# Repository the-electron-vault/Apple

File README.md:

# Apple

## Overview
This repository contains resources relating to Apple products.

## Disclaimer
The information contained in this repository has been generated via reverse-engineering of publicly available material, and is provided without warranty or guarantee of accuracy. [The Electron Vault](https://www.theelectronvault.com/) is not responsible for any losses or damages caused to equipment as a consequence of the information contained in this repository or associated documents.

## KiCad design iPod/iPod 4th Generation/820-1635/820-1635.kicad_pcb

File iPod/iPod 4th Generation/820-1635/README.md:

# 820-1635 iPod 4th Generation (Monochrome) Headphone/Hold Switch Board

## Overview
This is an open-source, KiCad-based 820-1635 PCBA that has been reverse-engineered from a physical board. This is the Headphone Jack and Hold Switch board used in the 4th Generation Monochrome iPod.

## Disclaimer
The information contained in this repository has been generated via reverse-engineering of publicly available material, and is provided without warranty or guarantee of accuracy. [The Electron Vault](https://www.theelectronvault.com/) is not responsible for any losses or damages caused to equipment as a consequence of the information contained in this repository or associated documents.

## Setup
### Database Library
This project uses a local database library for all components. As the library is linked to the project through relative pathing, it should just work once the ODBC driver is installed.
1) Install an ODBC driver. I use this one http://www.ch-werner.de/sqliteodbc/
2) [Optional] Install an SQLite database editor. I use SQLiteStudio https://sqlitestudio.pl

### Theme
This KiCad project has a number of thematic customisations. These are however completely optional and everything *should* work fine with the default theme. If you however wish to install the theme, here is the procedure:
1) Install KiCad as normal.
2) Copy PREF/color/Black and White.json from the repo into the corresponding folder in your KiCad preferences.
3) Launch KiCad and open Preferences -> Colors.
4) The Black and White theme should now be available in Schematic Editor -> Colors and PCB Editor -> Colors.
5) Schematic font: Arial

## Known Limitations
As this is a reverse-engineered design, there are several limitations potentially affecting accuracy that must be acknowledged:
- **This board is not ready for production.** The intent was to make it visually accurate enough to assist with troubleshooting and repair. OpenBoardView (Landrex-BRD) compatible files (generated using [kicad-boardview](https://github.com/whitequark/kicad-boardview) exporter) are provided in the repo along with PDF schematics.
- Component placement is only photographically accurate - there may be mechanical interferences.
- Board outline is best-effort. Use at your own risk.
- Board stackup is best effort; likely 4-layer.
- All routing is best-effort **and incomplete**, primarily as a checklist aid/sanity check that nets have been assigned to the correct components. There are missing elements such as internal planes/poly-pours.
- Trace widths are purely photographically scaled.
- Passive component (resistors, capacitors) values were measured with an LCR meter and rounded to the nearest standard value. Accuracy is not guaranteed.
- Some effort was made to characterise ferrite beads. The VNA scans can be found in the DOC folder. The part numbers captured in the schematic are **equivalent substitutes based on these scans and provided without guarantee.**
- The original part numbers for the buzzer, spring contacts, and hold switch were not able to be identified and thus equivalent substitutes were used.

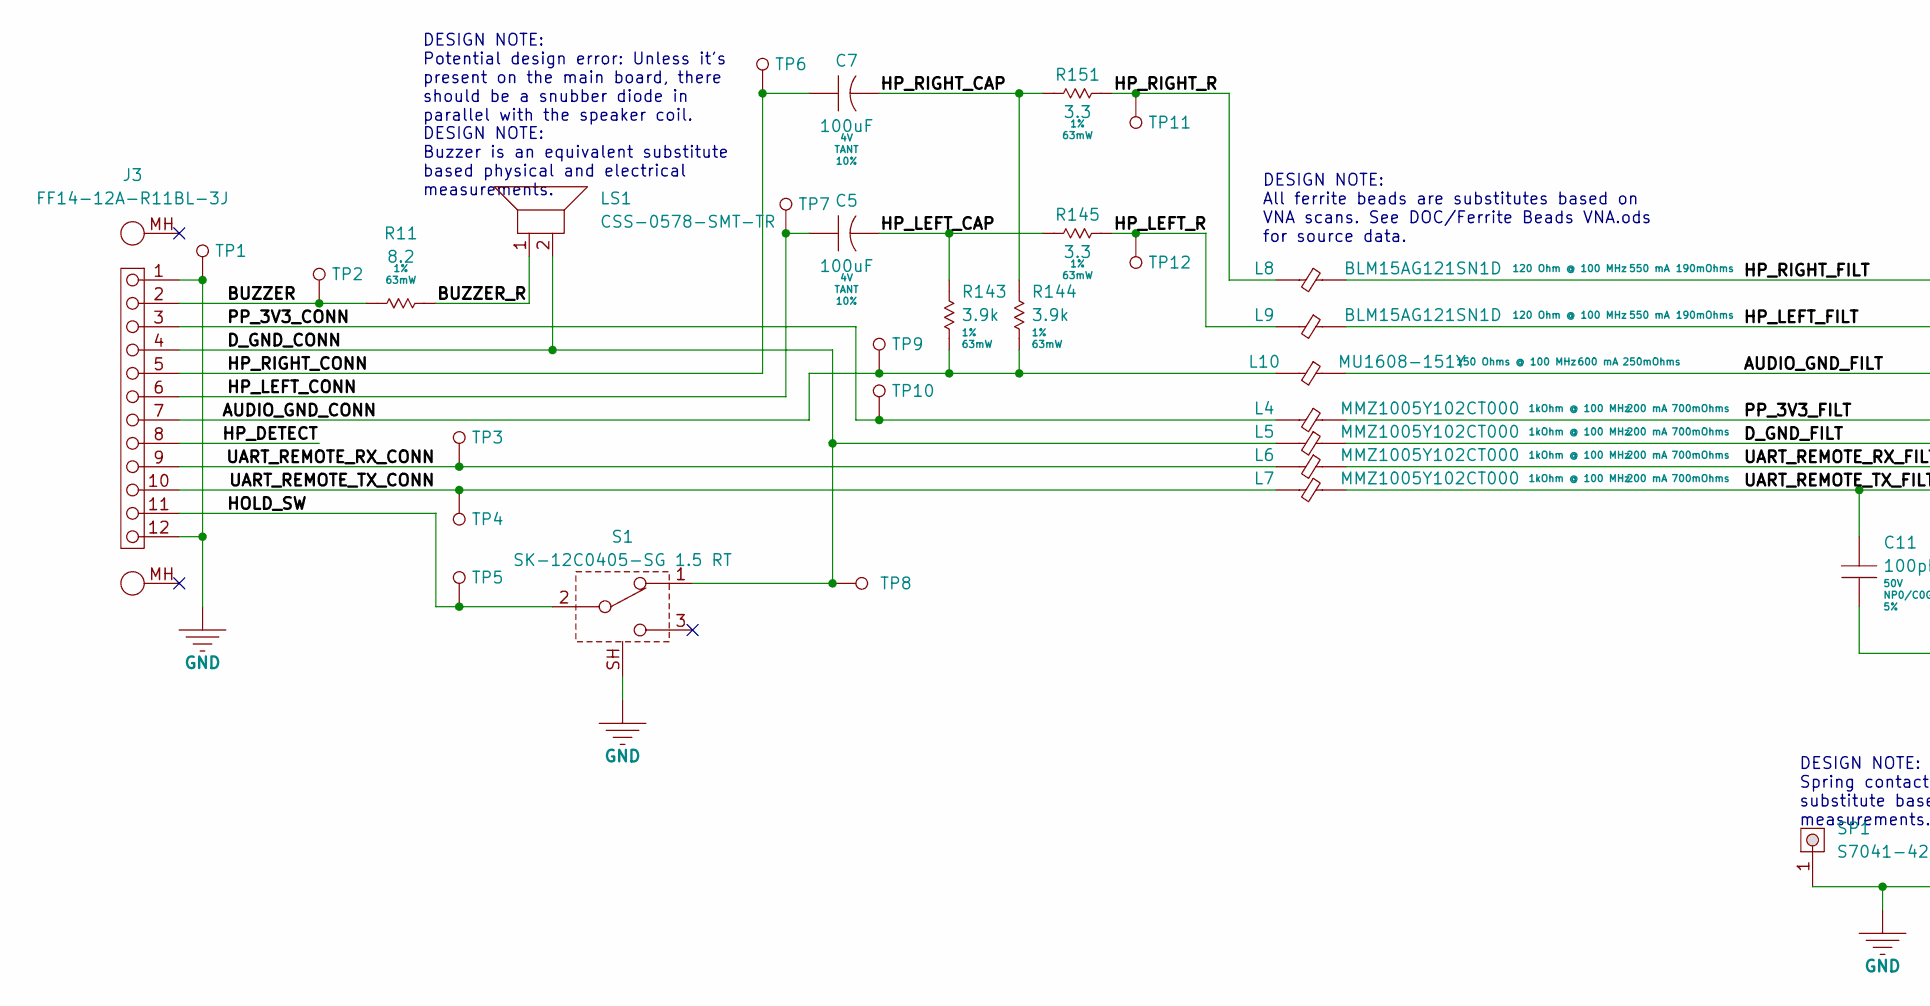
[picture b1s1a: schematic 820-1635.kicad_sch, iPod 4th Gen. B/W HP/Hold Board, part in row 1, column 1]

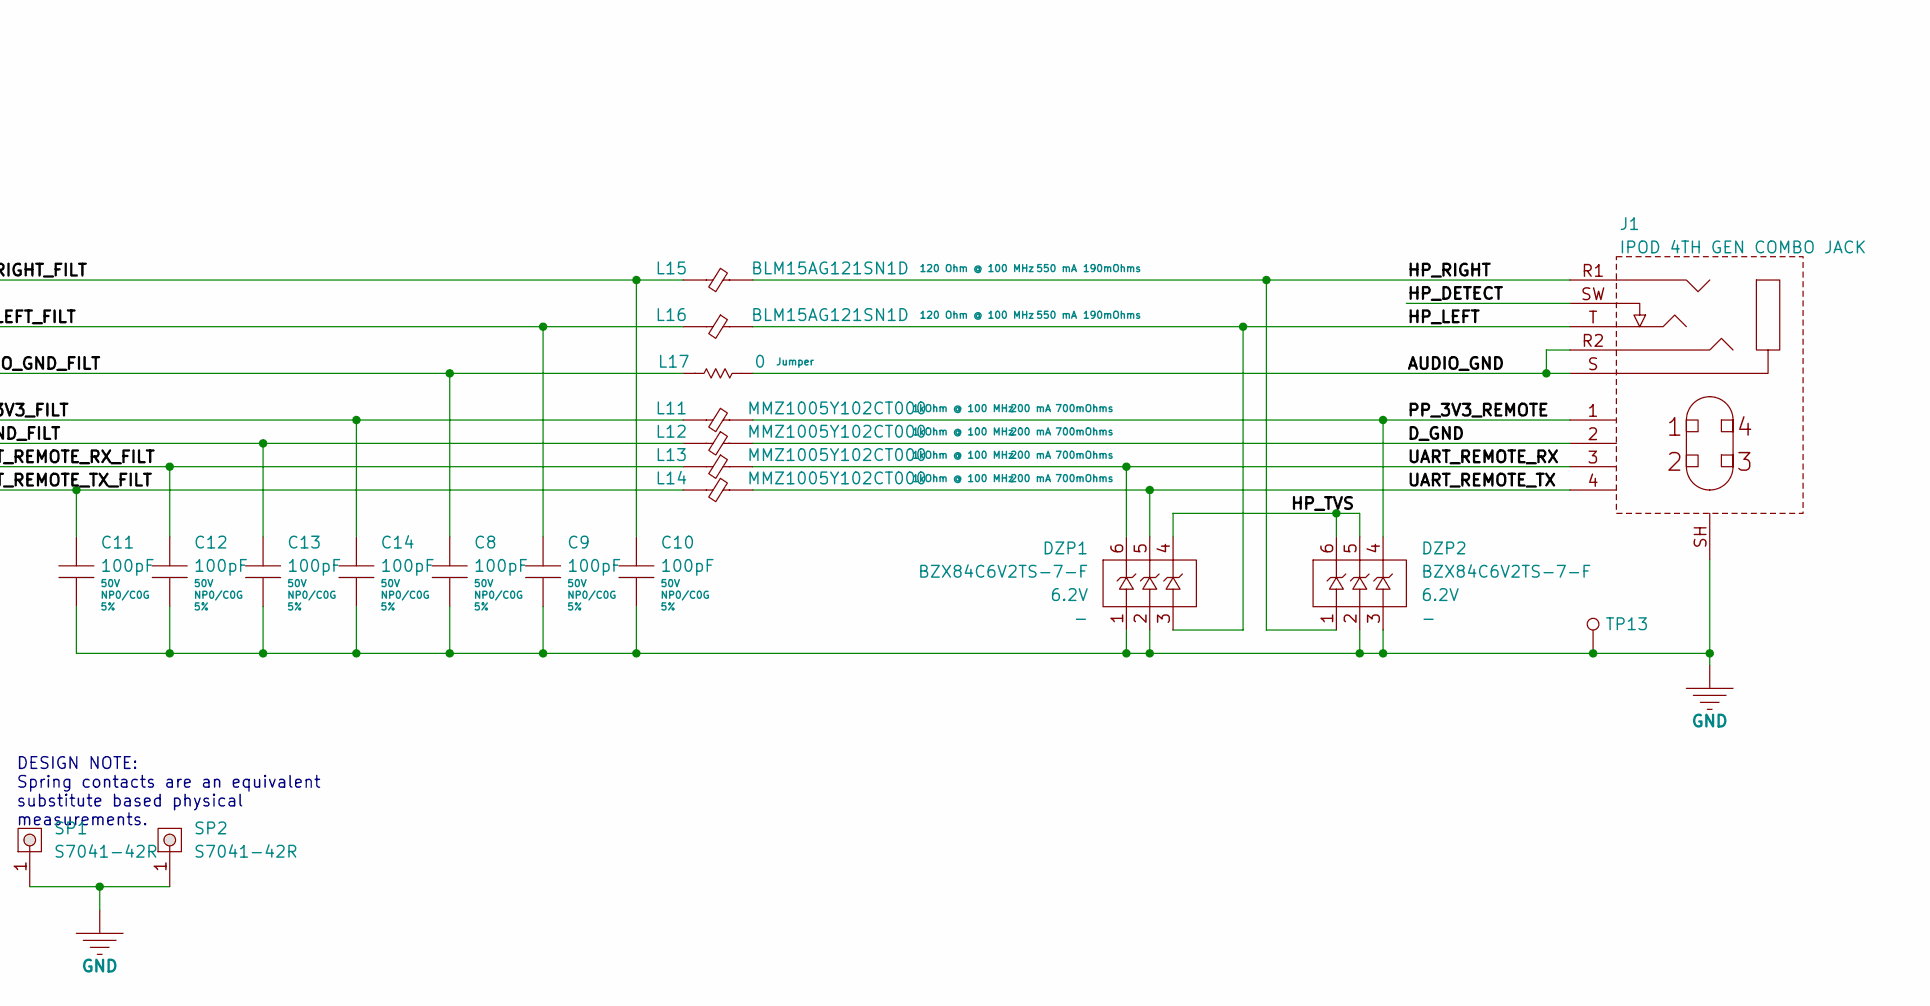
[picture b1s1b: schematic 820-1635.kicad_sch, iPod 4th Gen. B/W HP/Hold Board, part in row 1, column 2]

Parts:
C5, C7: 100uF; TPS-B; Voltage 4V; Tolerance 10%; Manufacturer Part Number TPSB107K004R0250
C8, C9, C10, C11, C12, C13, C14: 100pF; MLCC-0402; Voltage 50V; Tolerance 5%; Manufacturer Part Number CL05C101JB5NNNC
DZP1, DZP2: BZX84C6V2TS-7-F; SOT-363; Voltage 6.2V; Manufacturer Part Number BZX84C6V2TS-7-F
J1: IPOD 4TH GEN COMBO JACK; COMBO-JACK; Manufacturer Part Number IPOD 4TH GEN COMBO JACK
J3: FF14-12A-R11BL-3J; FF14-12A-R11B; Manufacturer Part Number FF14-12A-R11BL-3J
L4, L5, L6, L7, L11, L12, L13, L14: MMZ1005Y102CT000; FB-0402; Manufacturer Part Number MMZ1005Y102CT000
L8, L9, L15, L16: BLM15AG121SN1D; FB-0402; Manufacturer Part Number BLM15AG121SN1D
L10: MU1608-151Y; FB-0603; Manufacturer Part Number MU1608-151Y
L17: 0; RES-0603; Tolerance Jumper; Manufacturer Part Number CRCW06030000Z0EA
LS1: CSS-0578-SMT-TR; Manufacturer Part Number CSS-0578-SMT-TR
R11: 8.2; RES-0402; Tolerance 1%; Manufacturer Part Number CRCW04028R20FKEDC
R143, R144: 3.9k; RES-0402; Tolerance 1%; Manufacturer Part Number CRCW04023K90FKEDC
R145, R151: 3.3; RES-0402; Tolerance 1%; Manufacturer Part Number CRCW04023R30FKEDC
S1: SK-12C0405-SG 1.5 RT; Manufacturer Part Number SK-12C0405-SG 1.5 RT
SP1, SP2: S7041-42R; Manufacturer Part Number S7041-42R
TP1, TP2, TP3, TP4, TP5, TP6, TP7, TP8, TP9, TP10, TP11, TP12, TP13: TP; TP-SMT-0.6mm

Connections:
/AUDIO_GND: J1.R2 (RING2), J1.S (SLEEVE), L17.2
/AUDIO_GND_CONN: J3.7, L10.1, R143.2, R144.2, TP9.1
/AUDIO_GND_FILT: C8.1, L10.2, L17.1
/BUZZER: J3.2, R11.1, TP2.1
/BUZZER_R: LS1.1, R11.2
/D_GND: J1.2, L12.2
/D_GND_CONN: J3.4, L5.1, LS1.2, S1.1, TP8.1
/D_GND_FILT: C13.1, L5.2, L12.1
/HOLD_SW: J3.11, S1.2, TP5.1
/HP_DETECT: J1.SW (TIP_SWITCH), J3.8
/HP_LEFT: DZP1.3 (K2), J1.T (TIP), L16.2
/HP_LEFT_CAP: C5.2, R143.1, R145.1
/HP_LEFT_CONN: C5.1, J3.6, TP7.1
/HP_LEFT_FILT: C9.1, L9.2, L16.1
/HP_LEFT_R: L9.1, R145.2, TP12.1
/HP_RIGHT: DZP2.1 (A1), J1.R1 (RING1), L15.2
/HP_RIGHT_CAP: C7.2, R144.1, R151.1
/HP_RIGHT_CONN: C7.1, J3.5, TP6.1
/HP_RIGHT_FILT: C10.1, L8.2, L15.1
/HP_RIGHT_R: L8.1, R151.2, TP11.1
/HP_TVS: DZP1.4 (C3), DZP2.5 (C2), DZP2.6 (C1)
/PP_3V3_CONN: J3.3, L4.1, TP10.1
/PP_3V3_FILT: C14.1, L4.2, L11.1
/PP_3V3_REMOTE: DZP2.4 (C3), J1.1, L11.2
/UART_REMOTE_RX: DZP1.6 (C1), J1.3, L13.2
/UART_REMOTE_RX_CONN: J3.9, L6.1, TP3.1
/UART_REMOTE_RX_FILT: C12.1, L6.2, L13.1
/UART_REMOTE_TX: DZP1.5 (C2), J1.4, L14.2
/UART_REMOTE_TX_CONN: J3.10, L7.1, TP4.1
/UART_REMOTE_TX_FILT: C11.1, L7.2, L14.1
GND: C8.2, C9.2, C10.2, C11.2, C12.2, C13.2, C14.2, DZP1.1 (A1), DZP1.2 (S2), DZP2.2 (S2), DZP2.3 (K2), J1.SH, J3.1, J3.12, S1.SH, SP1.1, SP2.1, TP1.1, TP13.1

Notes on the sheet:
DESIGN NOTE: Potential design error: Unless it's present on the main board, there should be a snubber diode in parallel with the speaker coil.
DESIGN NOTE: Spring contacts are an equivalent substitute based physical measurements.
DESIGN NOTE: All ferrite beads are substitutes based on VNA scans. See DOC/Ferrite Beads VNA.ods for source data.
DESIGN NOTE: Buzzer is an equivalent substitute based physical and electrical measurements.

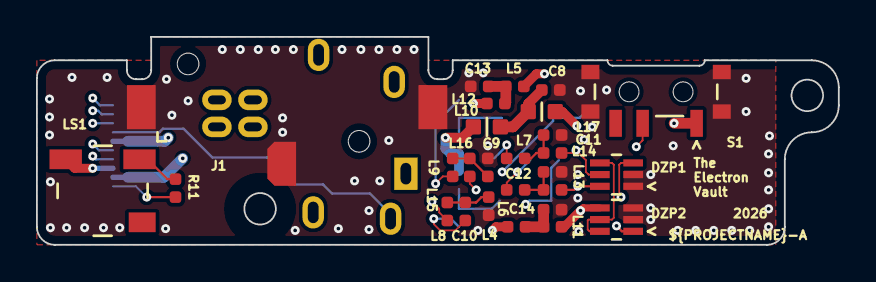
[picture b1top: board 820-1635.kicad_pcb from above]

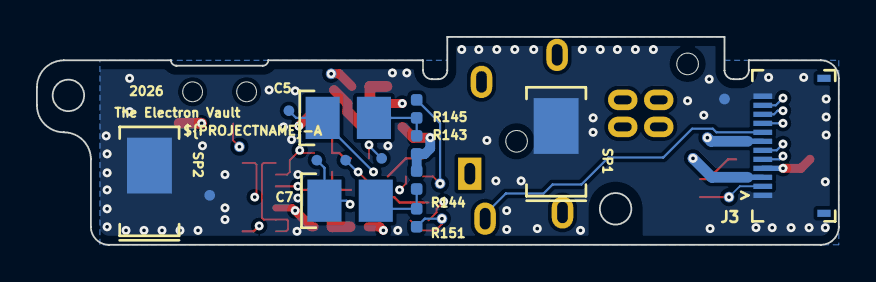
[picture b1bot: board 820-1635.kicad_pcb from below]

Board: 4 copper layers, 44.6 x 11.5 mm, 49 parts (22 on the bottom side), 31 nets.

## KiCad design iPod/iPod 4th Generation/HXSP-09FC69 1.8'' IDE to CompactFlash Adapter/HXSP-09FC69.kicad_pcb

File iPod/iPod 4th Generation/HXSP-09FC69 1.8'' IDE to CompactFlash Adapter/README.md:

# HXSP-09FC69 1.8" IDE to CompactFlash Adapter

## Overview
This is an open-source, KiCad-based 1.8" IDE to CompactFlash Adapter PCBA that has been reverse-engineered from a physical board. Though this is not an Apple part, it is included in this repository as it is frequently used when replacing the hard disk with a CompactFlash card on the 4th generation iPods (both Monochrome and Photo variants).

## Disclaimer
The information contained in this repository has been generated via reverse-engineering of publicly available material, and is provided without warranty or guarantee of accuracy. [The Electron Vault](https://www.theelectronvault.com/) is not responsible for any losses or damages caused to equipment as a consequence of the information contained in this repository or associated documents.

## Setup
### Database Library
This project uses a local database library for all components. As the library is linked to the project through relative pathing, it should just work once the ODBC driver is installed.
1) Install an ODBC driver. I use this one http://www.ch-werner.de/sqliteodbc/
2) [Optional] Install an SQLite database editor. I use SQLiteStudio https://sqlitestudio.pl

### Theme
This KiCad project has a number of thematic customisations. These are however completely optional and everything *should* work fine with the default theme. If you however wish to install the theme, here is the procedure:
1) Install KiCad as normal.
2) Copy PREF/color/Black and White.json from the repo into the corresponding folder in your KiCad preferences.
3) Launch KiCad and open Preferences -> Colors.
4) The Black and White theme should now be available in Schematic Editor -> Colors and PCB Editor -> Colors.
5) Schematic font: Arial

## Known Limitations
As this is a reverse-engineered design, there are several limitations potentially affecting accuracy that must be acknowledged:
- **This board is not ready for production.** The intent was to make it visually accurate enough to assist with troubleshooting, repair, and also for documenting the FPC pinout for any other projects that need it.
- Component placement is only photographically accurate - there may be mechanical interferences.
- Board outline is best-effort. Use at your own risk.
- The LED and resistor has been omitted because it's not critical; it just flashes with activity (DASP signal).
- The routing is *in theory* complete but provided without warranty.
- Trace widths are purely photographically scaled.
- No DRCs have been run on layout.

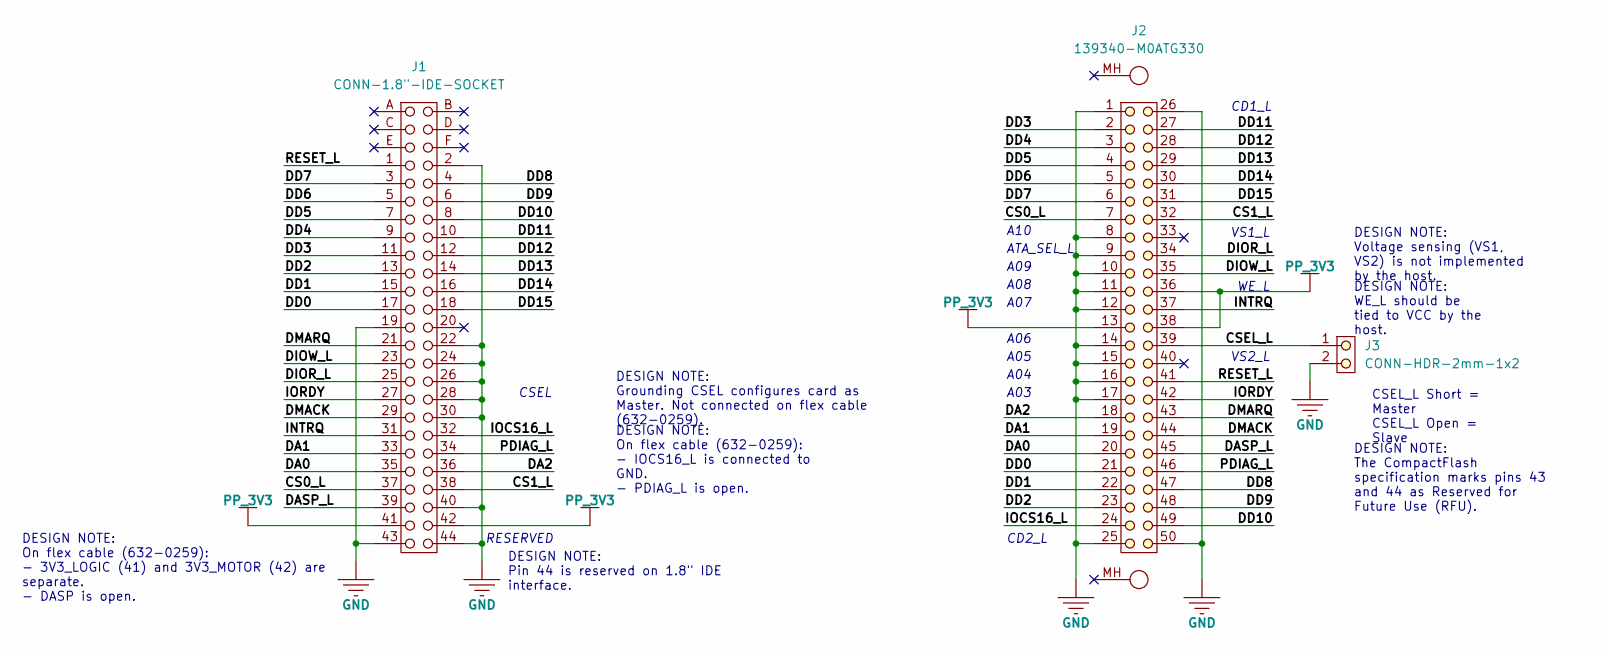
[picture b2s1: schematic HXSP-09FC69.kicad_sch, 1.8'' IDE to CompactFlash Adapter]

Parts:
J1: CONN-1.8"-IDE-SOCKET; CONN-1.8-IDE-SOCKET; Manufacturer Part Number CONN-1.8"-IDE-SOCKET
J2: 139340-M0ATG330; Manufacturer Part Number 139340-M0ATG330
J3: CONN-HDR-2mm-1x2; Manufacturer Part Number CONN-HDR-2mm-1x2

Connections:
/CS0_L: J1.37, J2.7
/CS1_L: J1.38, J2.32
/CSEL_L: J2.39, J3.1
/DA0: J1.35, J2.20
/DA1: J1.33, J2.19
/DA2: J1.36, J2.18
/DASP_L: J1.39, J2.45
/DD0: J1.17, J2.21
/DD1: J1.15, J2.22
/DD2: J1.13, J2.23
/DD3: J1.11, J2.2
/DD4: J1.9, J2.3
/DD5: J1.7, J2.4
/DD6: J1.5, J2.5
/DD7: J1.3, J2.6
/DD8: J1.4, J2.47
/DD9: J1.6, J2.48
/DD10: J1.8, J2.49
/DD11: J1.10, J2.27
/DD12: J1.12, J2.28
/DD13: J1.14, J2.29
/DD14: J1.16, J2.30
/DD15: J1.18, J2.31
/DIOR_L: J1.25, J2.34
/DIOW_L: J1.23, J2.35
/DMACK: J1.29, J2.44
/DMARQ: J1.21, J2.43
/INTRQ: J1.31, J2.37
/IOCS16_L: J1.32, J2.24
/IORDY: J1.27, J2.42
/PDIAG_L: J1.34, J2.46
/RESET_L: J1.1, J2.41
GND: J1.2, J1.19, J1.22, J1.24, J1.26, J1.28, J1.30, J1.40, J1.43, J1.44, J2.1, J2.8, J2.9, J2.10, J2.11, J2.12, J2.14, J2.15, J2.16, J2.17, J2.25, J2.26, J2.50, J3.2
PP_3V3: J1.41, J1.42, J2.13, J2.36, J2.38

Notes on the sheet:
DESIGN NOTE: Voltage sensing (VS1, VS2) is not implemented by the host.
DESIGN NOTE: Grounding CSEL configures card as Master. Not connected on flex cable (632-0259).
CSEL_L Short = Master CSEL_L Open = Slave
DESIGN NOTE: WE_L should be tied to VCC by the host.
DESIGN NOTE: On flex cable (632-0259): - 3V3_LOGIC (41) and 3V3_MOTOR (42) are separate. - DASP is open.
DESIGN NOTE: On flex cable (632-0259): - IOCS16_L is connected to GND. - PDIAG_L is open.
DESIGN NOTE: Pin 44 is reserved on 1.8" IDE interface.
DESIGN NOTE: The CompactFlash specification marks pins 43 and 44 as Reserved for Future Use (RFU).
A07
CD1_L
A10
WE_L
A06
CSEL
VS1_L
A05
A08
A09
VS2_L
RESERVED
A04
A03
ATA_SEL_L
CD2_L

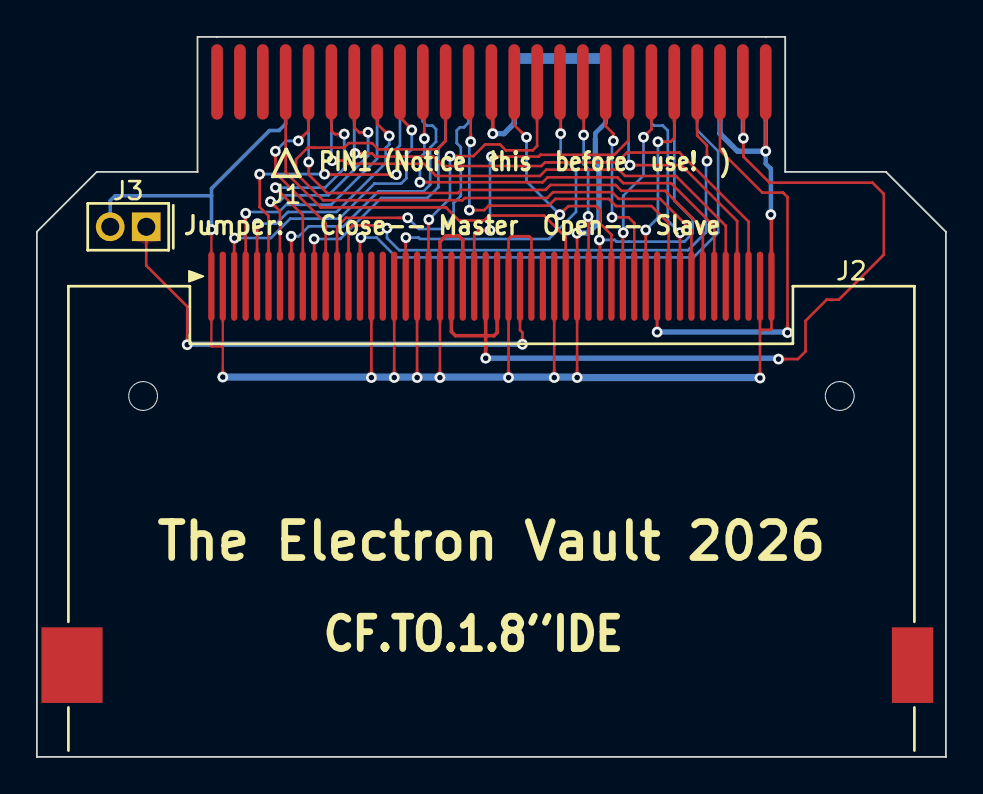
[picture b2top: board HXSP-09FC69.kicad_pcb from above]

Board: 2 copper layers, 50.5 x 40.0 mm, 3 parts (0 on the bottom side), 34 nets.

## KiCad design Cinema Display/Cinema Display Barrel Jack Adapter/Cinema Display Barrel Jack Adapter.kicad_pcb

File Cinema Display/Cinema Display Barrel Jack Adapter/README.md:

# Apple Cinema Display Barrel Jack Adapter

## Overview
This is an adapter board that facilitates connection of the 20” (A1081), 23” (A1082) and 30” (A1083) Apple Cinema Displays to off-the-shelf/third-party power supplies with a barrel jack (5.5OD/2.1ID or 5.5OD/2.5ID).

## Disclaimer
The information contained in this repository has been generated via reverse-engineering of publicly available material, and is provided without warranty or guarantee of accuracy. [The Electron Vault](https://www.theelectronvault.com/) is not responsible for any losses or damages caused to equipment as a consequence of the information contained in this repository or associated documents.

## KiCad Project Setup
### Database Library
This project uses a local database library for all components. As the library is linked to the project through relative pathing, it should just work once the ODBC driver is installed.
1) Install an ODBC driver. I use this one http://www.ch-werner.de/sqliteodbc/
2) [Optional] Install an SQLite database editor. I use SQLiteStudio https://sqlitestudio.pl

### Theme
This KiCad project has a number of thematic customisations. These are however completely optional and everything *should* work fine with the default theme. If you however wish to install the theme, here is the procedure:
1) Install KiCad as normal.
2) Copy PREF/color/Black and White.json from the repo into the corresponding folder in your KiCad preferences.
3) Launch KiCad and open Preferences -> Colors.
4) The Black and White theme should now be available in Schematic Editor -> Colors and PCB Editor -> Colors.
5) Schematic font: Arial

## Manufacturing
The repository includes manufacturing files in the MFG directory which can be used for ordering boards from any PCB manufacturer (PCBWay, JLCPCB, etc.). **At the time of this repo's publication, these boards have not been manufactured, so these files are provided without any warranty or guarantee.** A basic verification of the edge connector geometry was however done by milling out the pattern from blank 0.8mm copper clad using a desktop CNC engraver. 

All ordering information is provided in the User_Drawings gerber layer, and is also provided below for ease of ordering:

|Parameter          |Value |
|-------------------|------|
|Length             | 25mm |
|Width              | 16mm |
|Layers             | 2    |
|Finished Thickness | 0.8mm|
|Minimum Track/Space| 6mil |
|Minimum Hole/Drill | 0.3mm|

The board is designed to be as low cost as possible. As a point of reference, inputting the board specifications into PCBWay, at the time writing, a panel of 15 boards were estimated at USD $5 plus shipping on 24 hour turn. This pricing is with HASL finish, which should suffice for low cycle counts of the board edge connector (the part that plugs into the Display's power connector). If however you anticipate frequent plugging/unplugging of this adapter, specifying a hard gold finish for the contact fingers is recommened. This will however drive up cost substantially.

## Assembly
Though most Chinese board houses offer assembly services, given this board only has one component (plus an optional 0603 resistor), hand assembly is likely better suited. No BOM document has been generated given the simplicty. Instead, part numbers are provided in the table below:

|Designator |Part Number           | Notes                     |
|-----------|----------------------|---------------------------|
|J2         | 54-00253             | For 5.5OD/2.1ID           |
|           | JACK-C-SMT-10A-RA(R) | Alternate for 5.5OD/2.1ID |
|           | 54-00254             | For 5.5OD/2.5ID           |
|           | JACK-L-SMT-10A-RA(R) | Alternate for 5.5OD/2.5ID |
|R1         | DNF                  | For 150W indication       |
|           | TBD                  | For 90W indication        |
|           | TBD                  | For 65W indication        |

For most cases, R1 can be left unfitted (DNF). This will emulate the 150W power supply for the 30" Cinema Display, which will also work on the 20" and 23" models. **If you leave R1 unfitted but use a power supply rated below 150W, you are doing so at your own risk. If the supply is not well designed for handling overload, you may permanently damage it by connecting it to a panel that requires more power than it can supply**. If you wish to emulate one of the smaller (65W/90W) bricks to ensure a lower rating supply isn't mistakenly used by a larger monitor, you will need to determine the appropriate resistor to populate on R1. I was not able to find a good reference for what value these should be. You should be able to measure this off an original power adapter my measuring the resistance between ID/SENSE and one of the GND pins.

## Enclosures
I originally considered designing this board to fit into an off-the-shelf Hammond-style enclosure. However I couldn't see a viable way for the average person to achieve an acceptable result for the port cut outs, particularly for the edge connector where alignment is critical to minimise risk of damage to the mating plug. I also considered making these front panels out of PCB material (can breakaway from the adatper board panel), however I couldn't find any enclosures that would work with this solution. Plus, it just made assembly more finicky.

In the end I opted for this bare board solution that plugs directly into the cable. To protect the board (and also firmly secure it to the plug), I recommend applying heatshrink over the entire assembly as shown below:

If however someone wants to go the route of designing a printable enclosure, the 3D model for the board is provided in the STEP directory.

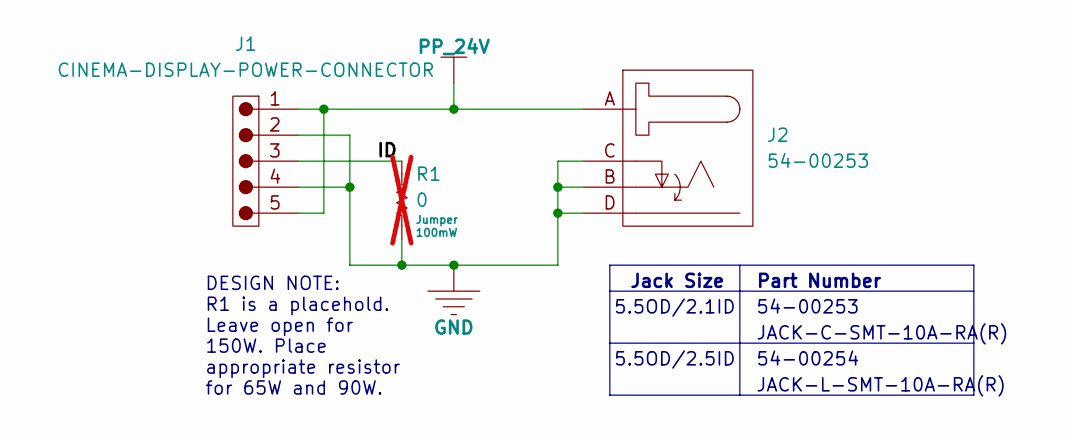
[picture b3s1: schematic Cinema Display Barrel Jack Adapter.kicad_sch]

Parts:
J1: CINEMA-DISPLAY-POWER-CONNECTOR; Manufacturer Part Number CINEMA-DISPLAY-POWER-CONNECTOR
J2: 54-00253; Manufacturer Part Number 54-00253
R1: 0; RES-0603; Tolerance Jumper; Manufacturer Part Number CRCW06030000Z0EBC; not fitted

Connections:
/ID: J1.3, R1.1
GND: J1.2, J1.4, J2.B, J2.C, J2.D, R1.2
PP_24V: J1.1, J1.5, J2.A

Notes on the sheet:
DESIGN NOTE: R1 is a placehold. Leave open for 150W. Place appropriate resistor for 65W and 90W.
JACK-C-SMT-10A-RA(R)
54-00254
Jack Size
5.5OD/2.1ID
JACK-L-SMT-10A-RA(R)
54-00253
5.5OD/2.5ID
Part Number

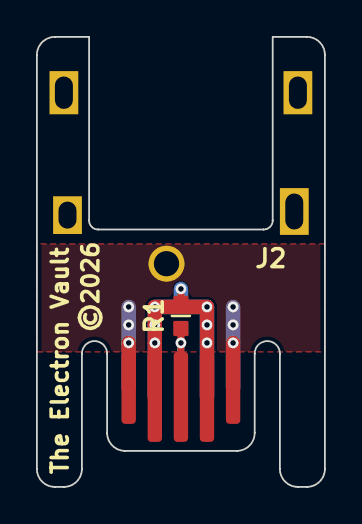
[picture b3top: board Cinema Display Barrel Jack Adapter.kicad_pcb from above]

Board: 2 copper layers, 16.0 x 25.0 mm, 3 parts (0 on the bottom side), 3 nets.

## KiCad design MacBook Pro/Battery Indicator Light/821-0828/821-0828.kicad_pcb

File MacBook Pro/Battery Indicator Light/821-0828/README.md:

# 821-0828 A1278 Battery Indicator Light Flex

## Overview
This is an open-source, KiCad-based 821-0828 PCBA that has been reverse-engineered from a physical board. This is the flex assembly used for indicating battery level on the side of the A1278 13" MacBook Pro. The LTC3219 LED driver is configured over I2C/SMBUS. The flex also hosts an omnidirectional magnetic (Hall effect) switch (AH1802) that is used for sensing the clamshell state.

## Disclaimer
The information contained in this repository has been generated via reverse-engineering of publicly available material, and is provided without warranty or guarantee of accuracy. [The Electron Vault](https://www.theelectronvault.com/) is not responsible for any losses or damages caused to equipment as a consequence of the information contained in this repository or associated documents.

## Setup
### Database Library
This project uses a local database library for all components. As the library is linked to the project through relative pathing, it should just work once the ODBC driver is installed.
1) Install an ODBC driver. I use this one http://www.ch-werner.de/sqliteodbc/
2) [Optional] Install an SQLite database editor. I use SQLiteStudio https://sqlitestudio.pl

### Theme
This KiCad project has a number of thematic customisations. These are however completely optional and everything *should* work fine with the default theme. If you however wish to install the theme, here is the procedure:
1) Install KiCad as normal.
2) Copy PREF/color/Black and White.json from the repo into the corresponding folder in your KiCad preferences.
3) Launch KiCad and open Preferences -> Colors.
4) The Black and White theme should now be available in Schematic Editor -> Colors and PCB Editor -> Colors.
5) Schematic font: Arial

## Known Limitations
As this is a reverse-engineered design, there are several limitations potentially affecting accuracy that must be acknowledged:
- **This board is not ready for production.** The intent was to make it visually accurate enough to assist with troubleshooting, repair, or as a reference design to facilitate the design of drop-in replacements or other similar projects. OpenBoardView (Landrex-BRD) compatible files (generated using [kicad-boardview](https://github.com/whitequark/kicad-boardview) exporter) are provided in the repo along with PDF schematics.
	- Component placement is only photographically accurate - there may be mechanical interferences.
	- Board outline is best-effort. Use at your own risk.
	- The stackup (2L PI flex with black coverlay) is *in theory* correct, but provided without warranty.
	- Stiffener detail (PI behind mezzanine connector and FR-4 around magnetic switch area) is **not** provided.
	- The routing is *in theory* complete but provided without warranty.
	- Trace widths are purely photographically scaled.
- Passive component (resistors, capacitors) values were measured with an LCR meter and rounded to the nearest standard value. Accuracy is not guaranteed.

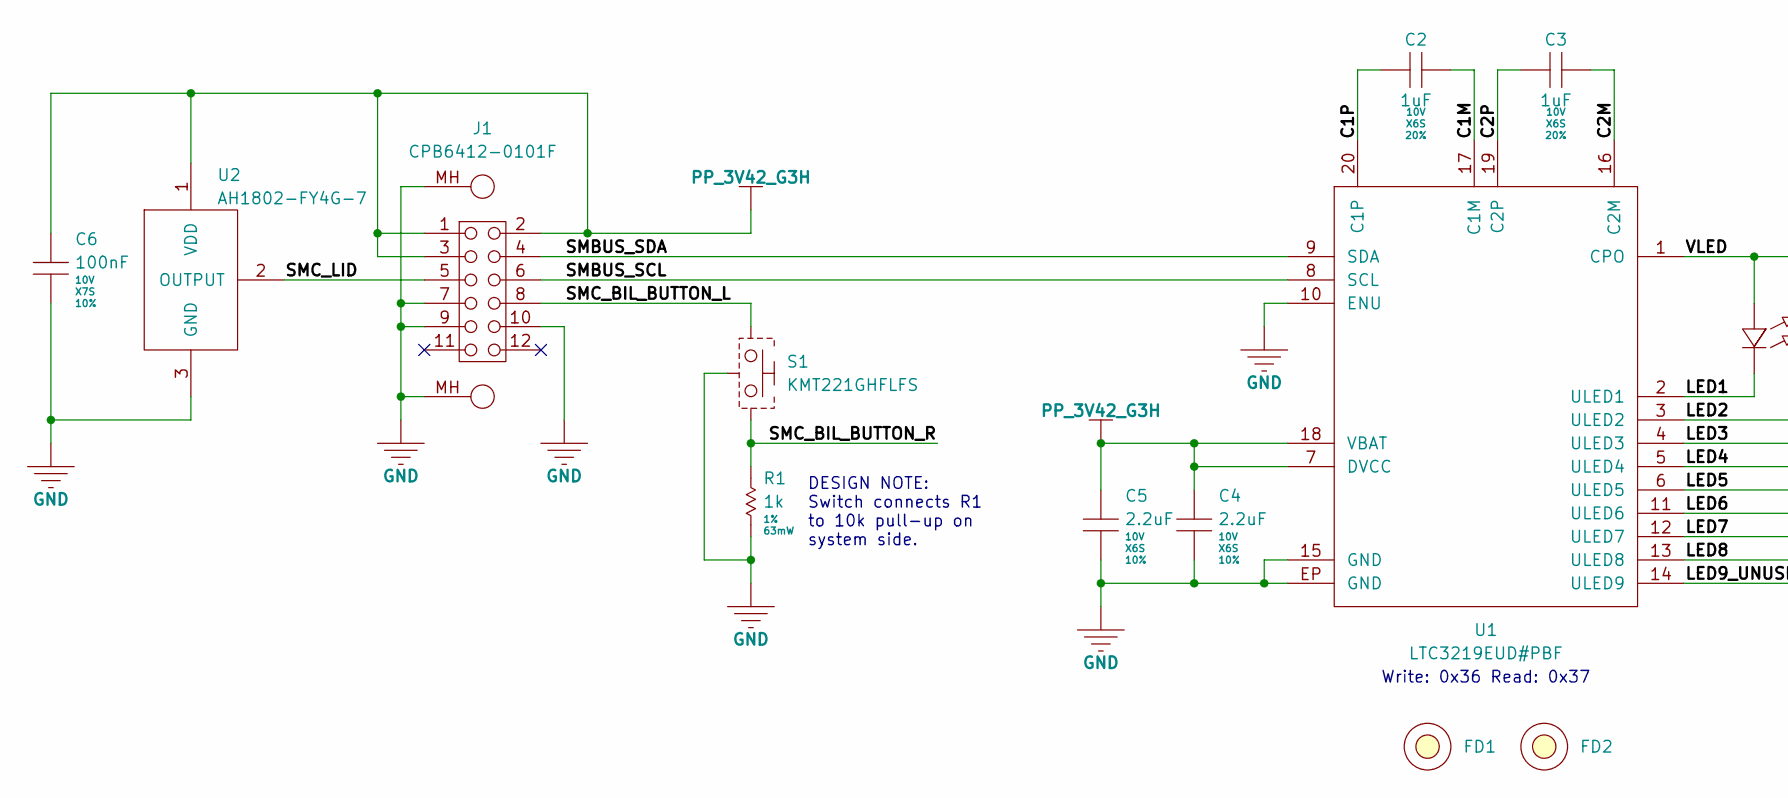
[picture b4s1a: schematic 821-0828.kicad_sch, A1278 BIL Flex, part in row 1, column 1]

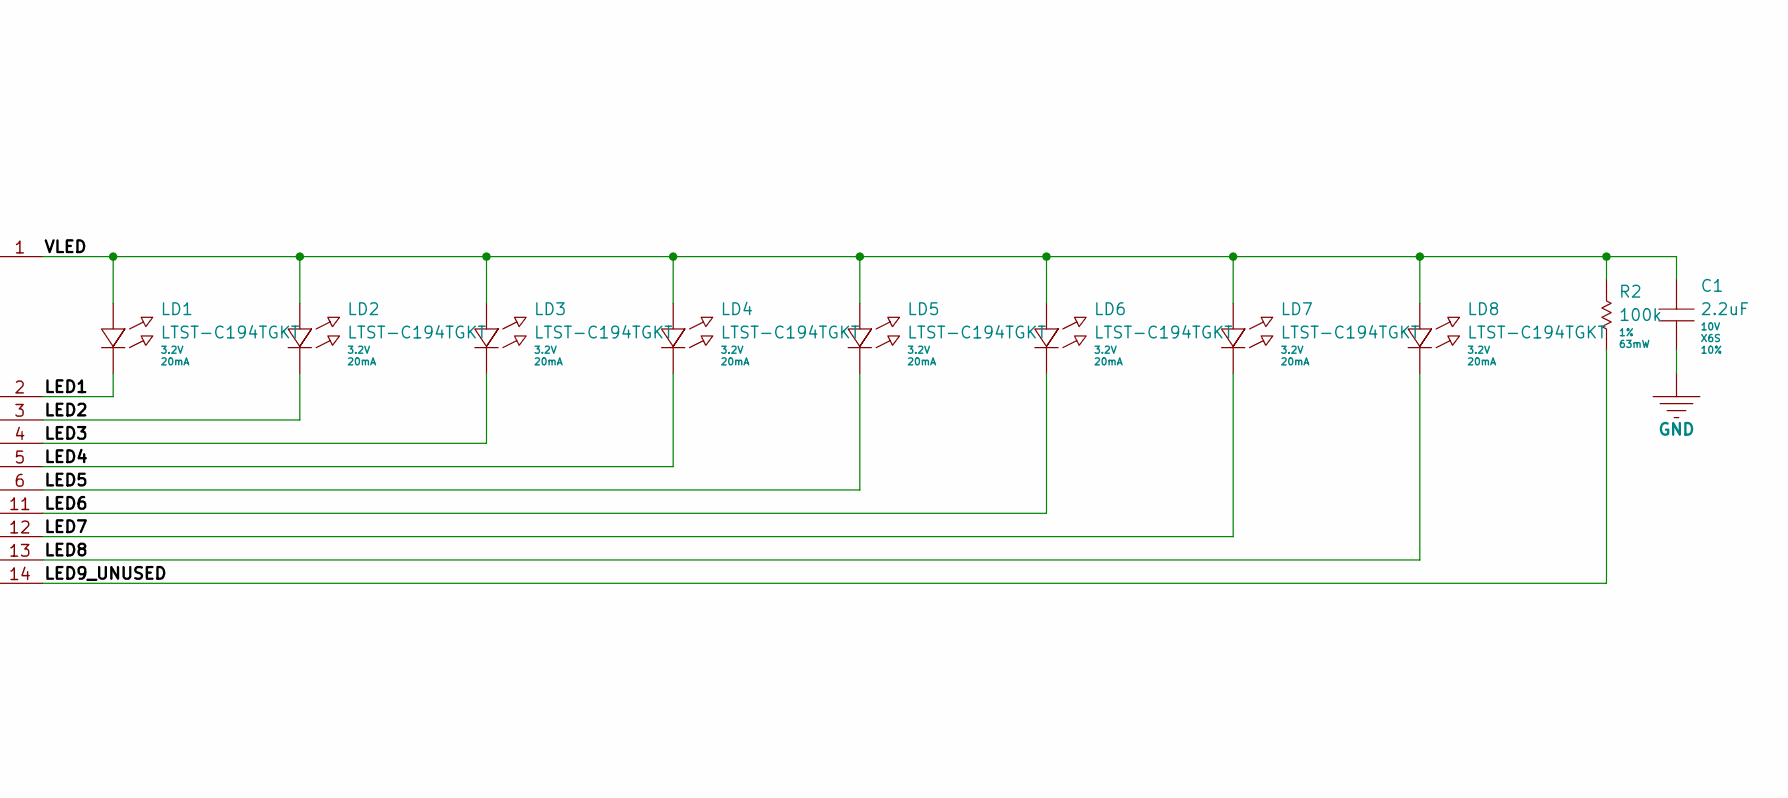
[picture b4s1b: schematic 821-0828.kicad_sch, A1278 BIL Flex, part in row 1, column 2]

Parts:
C1, C4, C5: 2.2uF; MLCC-0402; Voltage 10V; Tolerance 10%; Manufacturer Part Number GRM155C81A225KE44D
C2, C3: 1uF; MLCC-0402; Voltage 10V; Tolerance 20%; Manufacturer Part Number GRM155C81A105MA12D
C6: 100nF; MLCC-0201; Voltage 10V; Tolerance 10%; Manufacturer Part Number GRM033C71A104KE14J
FD1, FD2: FD; FIDUCIAL
J1: CPB6412-0101F; Manufacturer Part Number CPB6412-0101F
LD1, LD2, LD3, LD4, LD5, LD6, LD7, LD8: LTST-C194TGKT; Voltage 3.2V; Manufacturer Part Number LTST-C194TGKT
R1: 1k; RES-0402; Tolerance 1%; Manufacturer Part Number CRCW04021K00FKED
R2: 100k; RES-0402; Tolerance 1%; Manufacturer Part Number CRCW0402100KFKED
S1: KMT221GHFLFS; KMT2xxGHFLFx; Manufacturer Part Number KMT221GHFLFS
U1: LTC3219EUD#PBF; LT-UD-20; Manufacturer Part Number LTC3219EUD#PBF
U2: AH1802-FY4G-7; X2-DFN2015-3; Manufacturer Part Number AH1802-FY4G-7

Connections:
/C1M: C2.2, U1.17 (C1M)
/C1P: C2.1, U1.20 (C1P)
/C2M: C3.2, U1.16 (C2M)
/C2P: C3.1, U1.19 (C2P)
/LED1: LD1.K, U1.2 (ULED1)
/LED2: LD2.K, U1.3 (ULED2)
/LED3: LD3.K, U1.4 (ULED3)
/LED4: LD4.K, U1.5 (ULED4)
/LED5: LD5.K, U1.6 (ULED5)
/LED6: LD6.K, U1.11 (ULED6)
/LED7: LD7.K, U1.12 (ULED7)
/LED8: LD8.K, U1.13 (ULED8)
/LED9_UNUSED: R2.2, U1.14 (ULED9)
/SMBUS_SCL: J1.6, U1.8 (SCL)
/SMBUS_SDA: J1.4, U1.9 (SDA)
/SMC_BIL_BUTTON_L: J1.8, S1.1
/SMC_BIL_BUTTON_R: R1.1, S1.2
/SMC_LID: J1.5, U2.2 (OUTPUT)
/VLED: C1.1, LD1.A, LD2.A, LD3.A, LD4.A, LD5.A, LD6.A, LD7.A, LD8.A, R2.1, U1.1 (CPO)
GND: C1.2, C4.2, C5.2, C6.2, J1.7, J1.9, J1.10, J1.MH, R1.2, S1.SH, U1.10 (ENU), U1.15 (GND), U1.EP (GND), U2.3 (GND)
PP_3V42_G3H: C4.1, C5.1, C6.1, J1.1, J1.2, J1.3, U1.7 (DVCC), U1.18 (VBAT), U2.1 (VDD)

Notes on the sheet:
DESIGN NOTE: Switch connects R1 to 10k pull-up on system side.
Write: 0x36 Read: 0x37

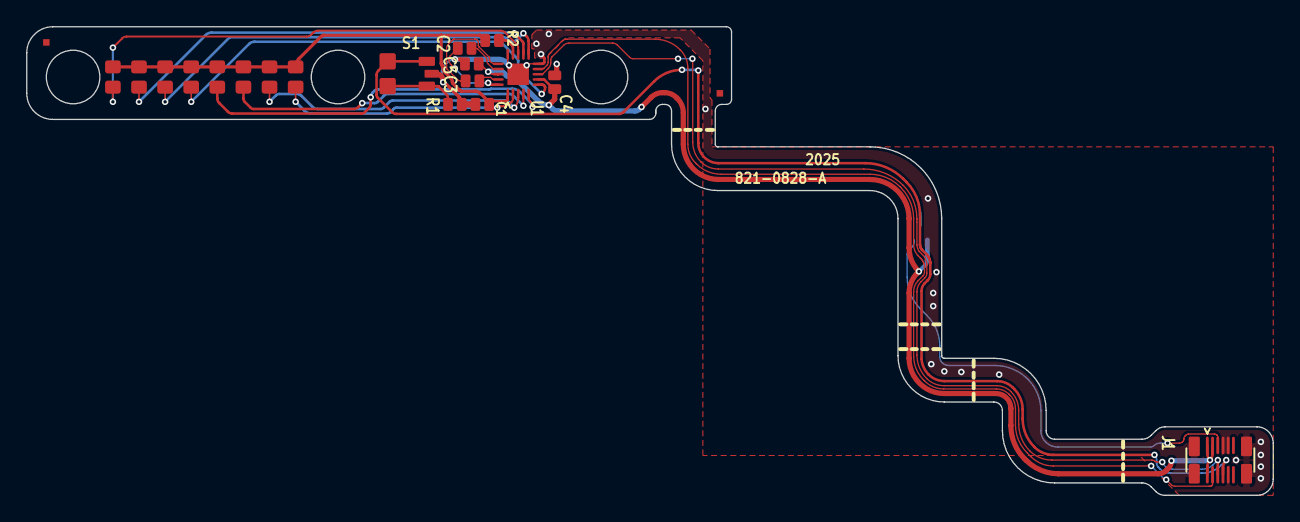
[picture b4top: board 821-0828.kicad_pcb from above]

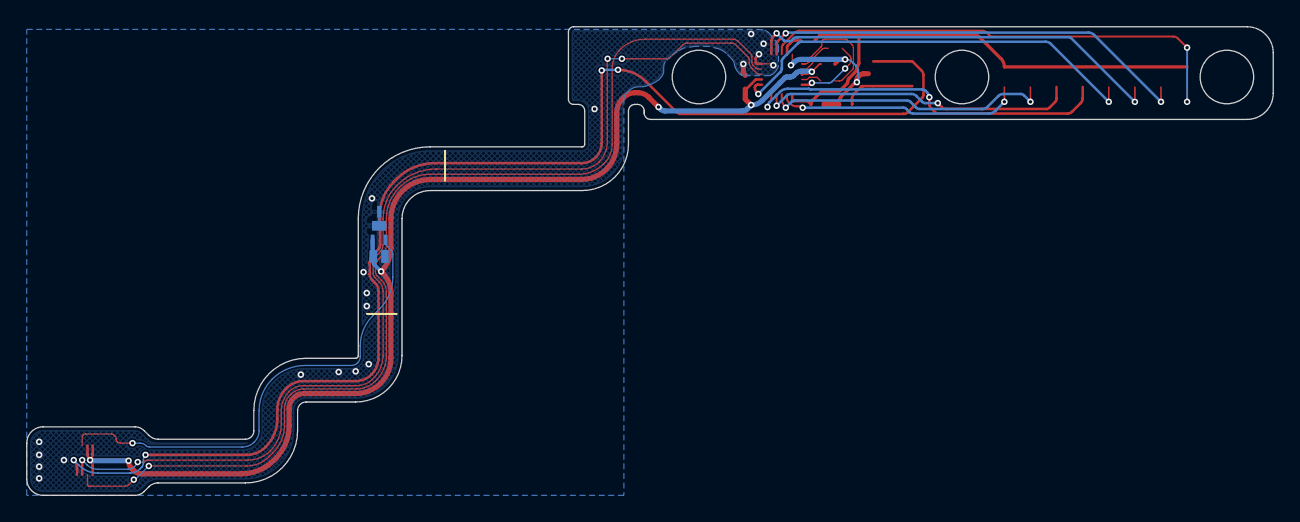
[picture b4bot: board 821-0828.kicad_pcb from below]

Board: 2 copper layers, 95.5 x 35.9 mm, 22 parts (2 on the bottom side), 21 nets.

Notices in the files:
Cinema Display/Cinema Display Barrel Jack Adapter/Cinema Display Barrel Jack Adapter.kicad_pcb:
©2026
